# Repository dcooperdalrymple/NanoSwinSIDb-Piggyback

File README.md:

# NanoSwinSIDb-Piggyback

Have a faulty 6581/8580 SID chip and need a replacement? The Nano SwinSIDb is a great (though I will admit, not best) choice, but it has one fatal flaw: lack of paddle support. Using this revision on the original Nano SwinSIDb design, you can "piggyback" your original SID chip with a faulty audio circuit and use some of it's secondary functions to add back in support for reading analog paddle inputs, external audio input, and random number generator while synthesizing music using the tried-and-true Nano SwinSIDb circuit.

## Building
The majority of the components are small SMD parts, but almost all of them can be hand-soldered with a steady hand. The only component that must be soldered using solder paste and a rework station is the active clock chip in a 3.2mm x 2.5mm package. Ensure you double check that no pads are bridged before soldering on the last part, the DIP-28 socket for the SID, because it will cover up a part of the board.

The same jumpers are provided as the original nano SwinSIDb for filter type (MOS6581/MOS8580) and output level (high/low). The jumpers are on by default to use a MOS6581 filter and have high output. You can cut them using an exacto knife to change the settings.

I use PCBWay to manufacture my boards, and all of the necessary files are provided that will be compatible with their services.

## Programming Firmware
A standard 6-Pin AVR ICSP header is provided on this board layout unlike the original Nano SwinSIDb. You shouldn't have to solder on a male pin header to program the board. Instead, I use a simple 6-pin cable from my programmer with a male end on it and hold it in place while flashing the chip.

Use the command `make flash` within the firmware directory to flash the copy of the SwinSID firmware with the ['Lazy' fix by Code Killer](http://www.forum64.de/index.php?thread/56605-nano-swinsid-upgrades-paddles-etc/&pageNo=2). Follow this by `make fuse` to ensure that the chip is configured correctly. The makefile utilizes avrdude with an Arduino ISP programmer on port `/dev/ttyACM0` _(linux environment)_. If this configuration doesn't work for you, either modify the Makefile or use your own flash programming environment to flash the provided firmware hex file or any other SwinSID compatible firmware.

## Additional Information
More information about building and programming your own board can be found at [tolaemon.com/nss](http://www.tolaemon.com/nss/). Most of the same principles should apply just with a few different parts. If you'd like to purchase one of these pre-built, I may have some available on my website, [dcdalrymple.com/NanoSwinSIDb-Piggyback/](https://dcdalrymple.com/NanoSwinSIDb-Piggyback/).

## Resources
- [SwinSID Analog Controller Hack](https://ilesj.wordpress.com/2014/07/24/swinsid-analog-controller-hack/)
- [nano SwinSIDb Tutorial](http://www.tolaemon.com/nss/)

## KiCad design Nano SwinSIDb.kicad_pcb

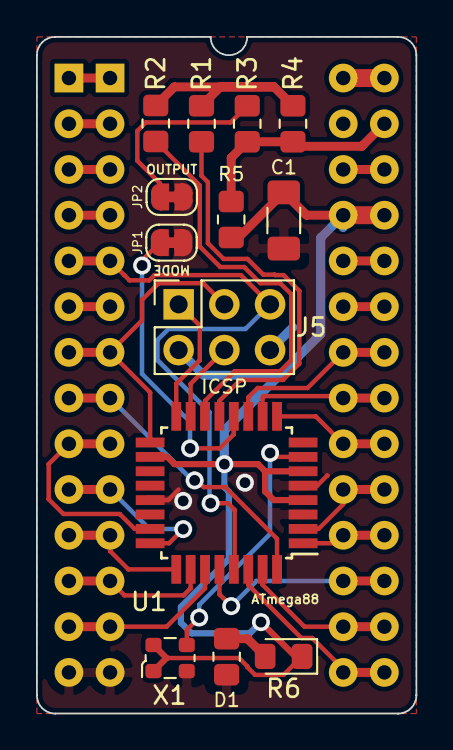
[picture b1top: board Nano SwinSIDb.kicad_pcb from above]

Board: 2 copper layers, 21.1 x 37.6 mm, 15 parts (0 on the bottom side), 37 nets.

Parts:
C1: 100nF; C_1206_3216Metric_Pad1.33x1.80mm_HandSolder
D1: Yellow; R_0805_2012Metric_Pad1.20x1.40mm_HandSolder
J5: 6PinConnector; PinSocket_2x03_P2.54mm_Vertical
JP1: ModeSelect; SolderJumper-2_P1.3mm_Bridged_RoundedPad1.0x1.5mm
JP2: OutputVoltage; SolderJumper-2_P1.3mm_Bridged_RoundedPad1.0x1.5mm
R1, R3: 1k; R_0805_2012Metric_Pad1.20x1.40mm_HandSolder
R2: 240k; R_0805_2012Metric_Pad1.20x1.40mm_HandSolder
R4: 2.2k; R_0805_2012Metric_Pad1.20x1.40mm_HandSolder
R5: 4.7k; R_0805_2012Metric_Pad1.20x1.40mm_HandSolder
R6: 330; LED_0805_2012Metric_Pad1.15x1.40mm_HandSolder
U1: ATmega88PA-AU; TQFP-32_7x7mm_P0.8mm
U2: 6581 Pins; DIP-28_W15.24mm
U3: 6581 Socket; DIP-28_W15.24mm_Socket
X1: ECS-3225MV; Oscillator_SMD_ECS_2520MV-xxx-xx-4Pin_2.5x2.0mm

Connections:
/6581SEL: JP1.1, U1.12
/A0: U1.23, U2.9, U3.9
/A1: U1.24, U2.10, U3.10
/A2: U1.25, U2.11, U3.11
/A3: U1.26, U2.12, U3.12
/A4: U1.27, U2.13, U3.13
/AUD1: R1.1, U1.13
/AUD2: R2.2, U1.14
/A_OUT: R3.1, R4.2, R5.2, U2.27
/CAP1A: U2.1, U3.1
/CAP1B: U2.2, U3.2
/CAP2A: U2.3, U3.3
/CAP2B: U2.4, U3.4
/D0: U1.30, U2.15, U3.15
/D1: U1.31, U2.16, U3.16
/D2: U1.28, U2.17, U3.17
/D3: U1.1, U2.18, U3.18
/D4: U1.2, U2.19, U3.19
/D5: U1.9, U2.20, U3.20
/D6: U1.10, U2.21, U3.21
/D7: U1.11, U2.22, U3.22
/EXT_IN: U2.26, U3.26
/MISO: J5.1, U1.16
/MOSI: J5.4, U1.15
/POTX: U2.24, U3.24
/POTY: U2.23, U3.23
/R~W~: J5.3, U1.17, U2.7, U3.7
/~CS~: U1.32, U2.8, U3.8
/~RES~: J5.5, U1.29, U2.5, U3.5
/Φ2: U2.6, U3.6
GND: C1.2, D1.1, J5.6, JP1.2, JP2.2, U1.3, U1.5, U1.21, U2.14, U3.14, X1.2
unnamed: D1.2, R6.2
unnamed: JP2.1, R3.2
unnamed: R1.2, R2.1, R4.1
unnamed: U1.7, X1.3
VCC: C1.1, J5.2, R5.1, R6.1, U1.4, U1.6, U1.18, U2.25, U3.25, X1.1, X1.4
VDD: U2.28, U3.28

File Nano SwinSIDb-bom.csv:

Source,/home/ogrecooper/repos/NanoSwinSIDb-Piggyback/Nano SwinSIDb.sch
Kicad Rev,Eeschema 5.1.9+dfsg1-1
Generated Date,Thu 04 Mar 2021 03:28:03 PM CST

Title,Not Set
Company,Not Set
Revision,Not Set
Date Issue,Not Set

Reference,Value,Library,Library Ref
U1,ATmega88PA-AU,MCU_Microchip_ATmega,ATmega88PA-AU
JP1,ModeSelect,Jumper,SolderJumper_2_Bridged
D1,Yellow,Device,LED
J5,6PinConnector,Connector,Conn_01x06_Female
C1,100nF,Device,CP
X1,ECS-3225MV,Oscillator,ECS-2520MV-xxx-xx
R6,330,Device,R_Small
TP1,TestPoint,Connector,TestPoint
TP2,TestPoint,Connector,TestPoint
TP3,TestPoint,Connector,TestPoint
R1,1k,Device,R_Small
R2,240k,Device,R_Small
R4,2.2k,Device,R_Small
R5,4.7k,Device,R_Small
R3,1k,Device,R_Small
JP2,OutputVoltage,Jumper,SolderJumper_2_Bridged
U3,6581 Socket,Nano-SwinSIDb-rescue,6581-65xx
U2,6581 Pins,Nano-SwinSIDb-rescue,6581-65xx

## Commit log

2021-02-24 Initial KiCad design work.
2021-02-24 First draft of PCB. Needs silkscreen work.
2021-03-03 Completed pcb design and gerber files for manufacture.
2021-03-12 Firmware added for use with Arduino ISP.
2021-03-22 Added images and updated readme.
2021-03-22 Update readme with purchase link.
2024-02-27 Added Tindie store badge to README.
